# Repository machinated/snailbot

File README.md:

# snailbot
Arduino compatible robot platform

## Hardware
List of parts:
 - electronic components listed in the [BOM file](pcb/BOM.csv)
 - HC-SR04 ultrasonic distance sensor
 - HC05 bluetooth adapter
 - 18650 lithium-ion battery
 - 2x 28BYJ-48 stepper motors

## Dependencies
- AccelStepper v.1.59

## Chassis
For better traction, use TPU for the tires.

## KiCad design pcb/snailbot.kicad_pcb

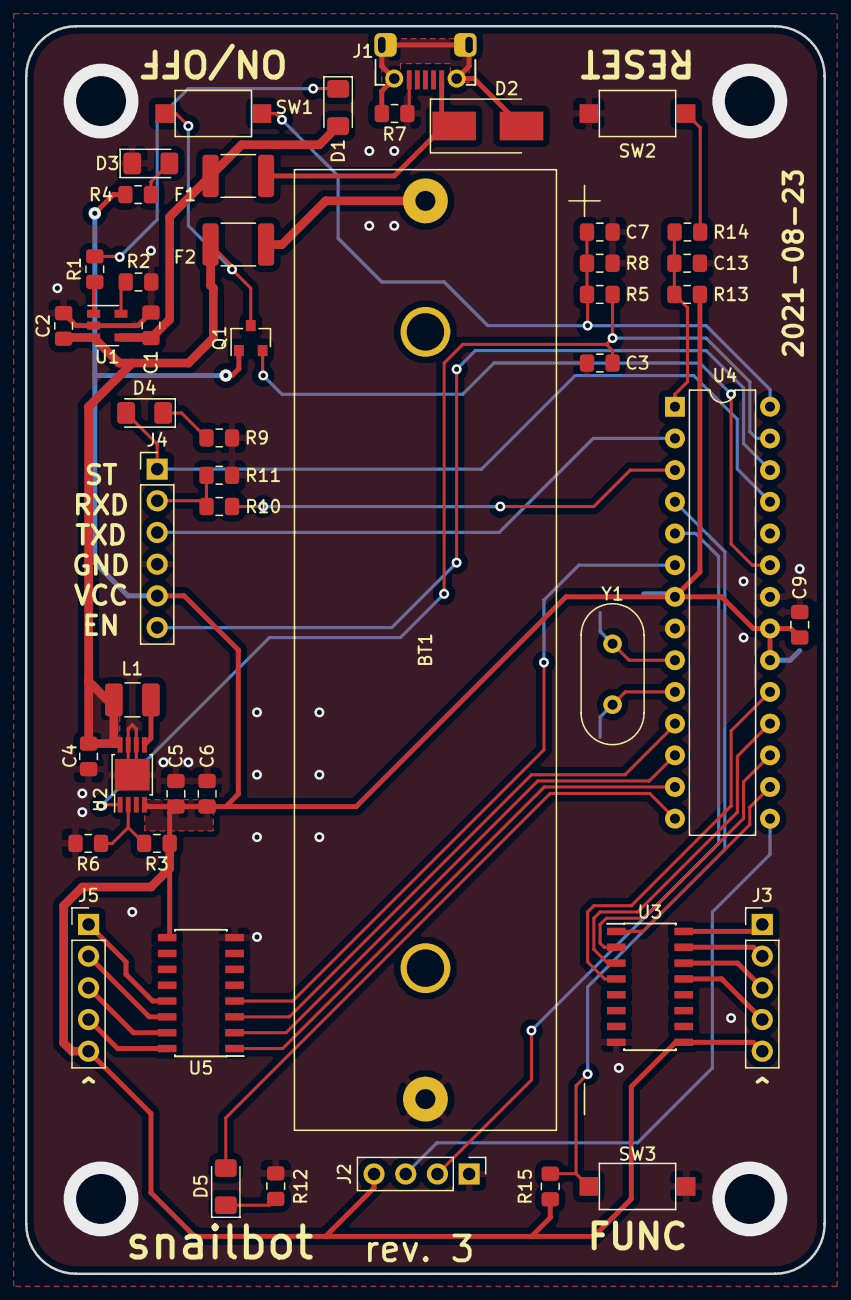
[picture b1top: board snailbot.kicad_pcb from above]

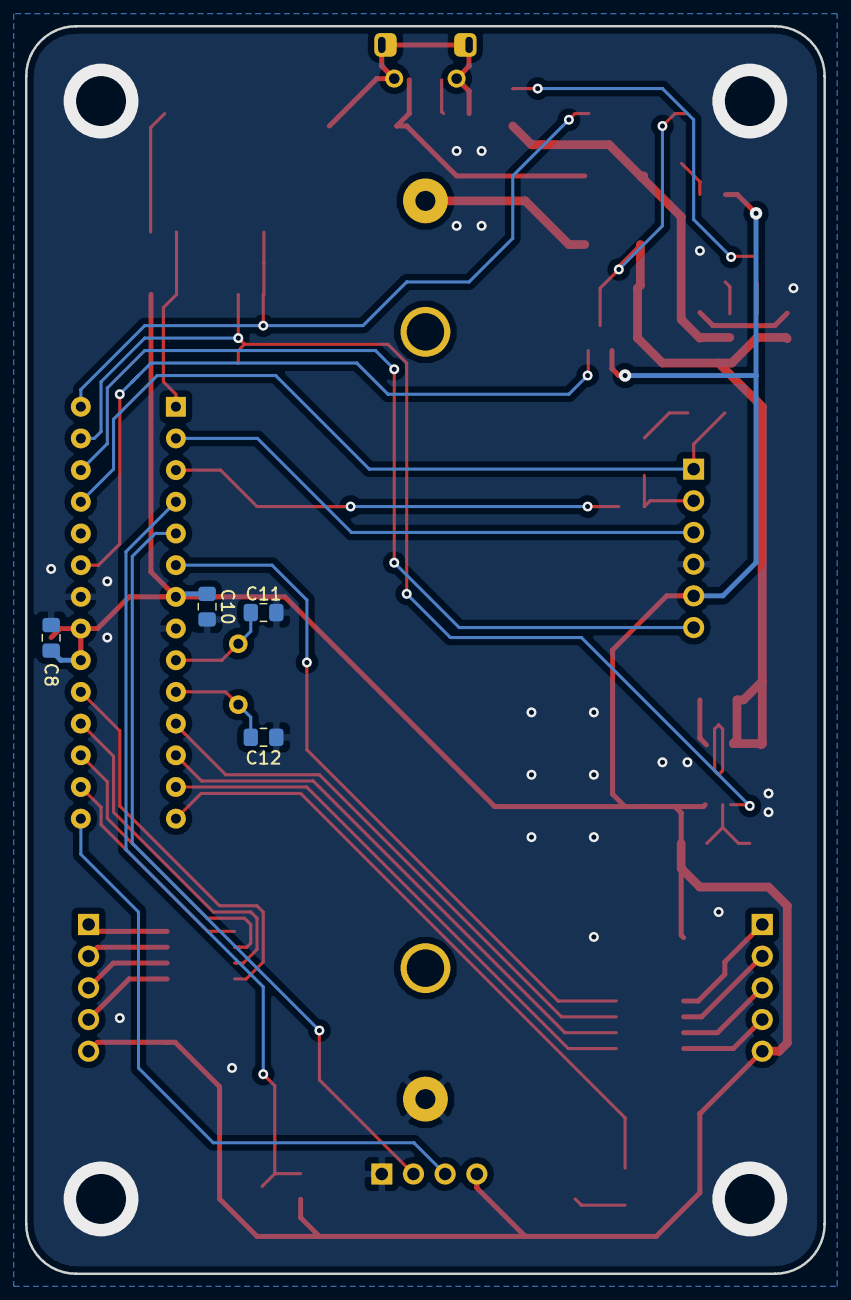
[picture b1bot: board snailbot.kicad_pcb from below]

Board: 2 copper layers, 64.0 x 100.0 mm, 52 parts (4 on the bottom side), 47 nets.

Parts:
BT1: Battery_Cell; BatteryHolder_1x18650
C1: 4u7; C_0805_2012Metric_Pad1.15x1.40mm_HandSolder
C2, C4, C5, C6, C7: 10u; C_0805_2012Metric_Pad1.15x1.40mm_HandSolder
C3: 10n; C_0805_2012Metric_Pad1.15x1.40mm_HandSolder
C8, C9, C10, C13: 100n; C_0805_2012Metric_Pad1.15x1.40mm_HandSolder
C11, C12: 22p; C_0805_2012Metric_Pad1.15x1.40mm_HandSolder
D1: RED; LED_1206_3216Metric_Pad1.42x1.75mm_HandSolder
D2: D_TVS; D_SMB_Handsoldering
D3: YELLOW; LED_1206_3216Metric_Pad1.42x1.75mm_HandSolder
D4, D5: BLUE; LED_1206_3216Metric_Pad1.42x1.75mm_HandSolder
F1: 750mA; Fuse_1812_4532Metric_Pad1.30x3.40mm_HandSolder
F2: 1A; Fuse_1812_4532Metric_Pad1.30x3.40mm_HandSolder
J1: USB_B_Micro; USB_Micro-B_MOLEX_105017-0001
J2: Conn_01x04_Female; PinHeader_1x04_P2.54mm_Vertical
J3, J5: Conn_01x05_Male; PinHeader_1x05_P2.54mm_Vertical
J4: Conn_01x06_Female; PinHeader_1x06_P2.54mm_Vertical
L1: 4u7; L_1210_3225Metric_Pad1.42x2.65mm_HandSolder
Q1: BSS138; SOT-23
R1, R7: 1k; R_0805_2012Metric_Pad1.15x1.40mm_HandSolder
R2: 2k2; R_0805_2012Metric_Pad1.15x1.40mm_HandSolder
R3: 470k 1%; R_0805_2012Metric_Pad1.15x1.40mm_HandSolder
R4, R9, R12: 470; R_0805_2012Metric_Pad1.15x1.40mm_HandSolder
R5: 1M; R_0805_2012Metric_Pad1.15x1.40mm_HandSolder
R6: 150k 1%; R_0805_2012Metric_Pad1.15x1.40mm_HandSolder
R8: 100k; R_0805_2012Metric_Pad1.15x1.40mm_HandSolder
R10, R13, R15: 10k; R_0805_2012Metric_Pad1.15x1.40mm_HandSolder
R11: 15k; R_0805_2012Metric_Pad1.15x1.40mm_HandSolder
R14: 100; R_0805_2012Metric_Pad1.15x1.40mm_HandSolder
SW1, SW2, SW3: SW_Push; SW_SPST_CK_RS282G05A3
U1: MCP73831-2-OT; SOT-23-5
U2: MCP1642B; MSOP-8-1EP_3x3mm_P0.65mm_EP2.54x2.8mm
U3, U5: ULN2003; SOIC-16_3.9x9.9mm_P1.27mm
U4: ATmega328P-PU; DIP-28_W7.62mm
Y1: 16MHz; Crystal_HC49-U_Vertical

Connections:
+BATT: C2.1, C4.1, F2.1, L1.2, Q1.3, SW1.1, U1.3, U2.8
GND: BT1.2, C1.2, C2.2, C3.1, C4.2, C5.2, C6.2, C7.2, C8.2, C9.1, C10.2, C11.1, C12.1, C13.2, D3.1, J1.5, J2.1, J4.4, R2.2, R6.2, R7.1, R8.1, R9.1, R11.1, R12.1, SW2.2, SW3.2, U1.2, U2.6, U2.7, U2.9, U3.8, U4.8, U4.22, U5.8
unnamed: BT1.1, F2.2
unnamed: C11.2, U4.9, Y1.1
unnamed: C12.2, U4.10, Y1.2
unnamed: C13.1, R13.1, R14.1, U4.1
unnamed: D1.1, R1.2
unnamed: D2.1, F1.2, J1.1
unnamed: D2.2, J1.6, R7.2
unnamed: D3.2, R4.1
unnamed: D4.1, R9.2
unnamed: D5.1, R12.2
unnamed: J3.1, U3.16
unnamed: J3.2, U3.15
unnamed: J3.3, U3.14
unnamed: J3.4, U3.13
unnamed: J4.2, R10.1, R11.2
unnamed: J5.1, U5.13
unnamed: J5.2, U5.14
unnamed: J5.3, U5.15
unnamed: J5.4, U5.16
unnamed: L1.1, U2.5
unnamed: R1.1, U1.1
unnamed: R2.1, U1.5
unnamed: R3.2, R6.1, U2.2
unnamed: R14.2, SW2.1
PB0: D5.2, U4.14
PB1: J2.3, U4.15
PB2: U3.1, U4.16
PB3: U3.2, U4.17
PB4: U3.3, U4.18
PB5: U3.4, U4.19
PC0: Q1.2, U4.23
PC2: D4.2, J4.1, U4.25
PC3: J4.6, U4.26
PC4: C3.2, R5.2, U2.1, U4.27
PC5: C7.1, R5.1, R8.2, SW1.2, U4.28
PD2: R15.1, SW3.1, U4.4
PD3: J2.2, U4.5
PD4: U4.6, U5.4
PD5: U4.11, U5.3
PD6: U4.12, U5.2
PD7: U4.13, U5.1
RXD: J4.3, U4.2
TXD: R10.2, U4.3
VCC: C5.1, C6.1, C8.1, C9.2, C10.1, J2.4, J3.5, J4.5, J5.5, Q1.1, R3.1, R4.2, R13.2, R15.2, U2.4, U3.9, U4.7, U4.20, U4.21, U5.9
VDD: C1.1, D1.2, F1.1, U1.4

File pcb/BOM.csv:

Item,Qty,Reference(s),Value,Footprint
1,1,BT1,Battery_Cell,mc_mech:BatteryHolder_1x18650
2,1,C1,4u7,Capacitor_SMD:C_0805_2012Metric_Pad1.15x1.40mm_HandSolder
3,5,"C2, C4, C5, C6, C7",10u,Capacitor_SMD:C_0805_2012Metric_Pad1.15x1.40mm_HandSolder
4,4,"C8, C9, C10, C13",100n,Capacitor_SMD:C_0805_2012Metric_Pad1.15x1.40mm_HandSolder
5,2,"C11, C12",22p,Capacitor_SMD:C_0805_2012Metric_Pad1.15x1.40mm_HandSolder
6,1,D1,RED,LED_SMD:LED_1206_3216Metric_Pad1.42x1.75mm_HandSolder
7,1,D2,D_TVS,Diode_SMD:D_SMB_Handsoldering
8,1,D3,YELLOW,LED_SMD:LED_1206_3216Metric_Pad1.42x1.75mm_HandSolder
9,2,"D4, D5",BLUE,LED_SMD:LED_1206_3216Metric_Pad1.42x1.75mm_HandSolder
10,1,F1,750mA,Fuse:Fuse_1812_4532Metric_Pad1.30x3.40mm_HandSolder
11,1,F2,1A,Fuse:Fuse_1812_4532Metric_Pad1.30x3.40mm_HandSolder
12,1,J1,USB_B_Micro,mc_mech:USB_Micro-B_MOLEX_105017-0001
13,1,J2,Conn_01x04_Female,Connector_PinHeader_2.54mm:PinHeader_1x04_P2.54mm_Vertical
14,2,"J3, J5",Conn_01x05_Male,Connector_PinHeader_2.54mm:PinHeader_1x05_P2.54mm_Vertical
15,1,J4,Conn_01x06_Female,Connector_PinHeader_2.54mm:PinHeader_1x06_P2.54mm_Vertical
16,1,L1,4u7,Inductor_SMD:L_1210_3225Metric_Pad1.42x2.65mm_HandSolder
17,3,"R4, R9, R12",470,Resistor_SMD:R_0805_2012Metric_Pad1.15x1.40mm_HandSolder
18,1,R2,2k2,Resistor_SMD:R_0805_2012Metric_Pad1.15x1.40mm_HandSolder
19,1,R3,470k 1%,Resistor_SMD:R_0805_2012Metric_Pad1.15x1.40mm_HandSolder
20,1,R5,1M,Resistor_SMD:R_0805_2012Metric_Pad1.15x1.40mm_HandSolder
21,1,R6,150k 1%,Resistor_SMD:R_0805_2012Metric_Pad1.15x1.40mm_HandSolder
22,2,"R1, R7",1k,Resistor_SMD:R_0805_2012Metric_Pad1.15x1.40mm_HandSolder
23,1,R8,100k,Resistor_SMD:R_0805_2012Metric_Pad1.15x1.40mm_HandSolder
24,3,"R10, R13, R15",10k,Resistor_SMD:R_0805_2012Metric_Pad1.15x1.40mm_HandSolder
25,1,R11,15k,Resistor_SMD:R_0805_2012Metric_Pad1.15x1.40mm_HandSolder
26,2,"R14, R16",100,Resistor_SMD:R_0805_2012Metric_Pad1.15x1.40mm_HandSolder
27,3,"SW1, SW2, SW3",SW_Push,Button_Switch_SMD:SW_SPST_CK_RS282G05A3
28,1,U1,MCP73831-2-OT,Package_TO_SOT_SMD:SOT-23-5
29,1,U2,MCP1642B,Package_SO:MSOP-8-1EP_3x3mm_P0.65mm_EP2.54x2.8mm
30,2,"U3, U5",ULN2003,Package_SO:SOIC-16_3.9x9.9mm_P1.27mm
31,1,U4,ATmega328P-PU,Package_DIP:DIP-28_W7.62mm
32,1,Y1,16MHz,Crystal:Crystal_HC49-U_Vertical

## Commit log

2021-08-10 Initial sources and designs
2021-08-10 Project description in README.md
2021-08-22 Fixed issues found in prototype
2021-08-22 Updated schematics and production files
